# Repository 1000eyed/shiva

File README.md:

# SHIVA
A 12U 40% keyboard supporting multiple layouts, offset space bar row, and LEDs.

## About

This keyboard supports as many different layouts as possible. Currently supported are: ortho, alpha stagger, uniform 0.25U stagger, normal stagger, plus multiple space row configurations. After all, you got 5 PCBs.
- designed around Gateron KS27/KS33 low profile switches.
- rotary encoder support.
- bluetooth connection only. USB connection possible with an appropriate case.
- leds to display connection/battery status.
- nice!nano MCU.
- ZMK keyboard firmware support.
- open source.

## KLE

See possible configurations below:

## How to build one

I provide all the production files you will need in order to assemble the keyboard. In [prod](prod/) folder you will find the PCB gerbers and STLs for case (only one configuration is supported now). I intended the case to be CNC'd from PC, however it is not tested yet and only 3D printed it so far. There are no build instructions, as everything should be self-explanatory.

### Part list
| #     | name                 | comments                                  |
|-------|----------------------|-------------------------------------------|
| 1     | main PCB             | Order at fabricator of your choice        |
| 1     | Nice!nano v2         | Controller board. Make sure you have enough sockets for all pins. |
| 1     | EC11                 | Rotary Encoder through hole style (optional)         |
| ~45   | 1N4148 - SOD-123     | Diodes                                    |
| 3     | LED 3mm              | Choose red, yellow (orange), and green        |
| 1     | MSK-12C02            | Power switch                              | 
| 1     | JST 1.25mm pitch     | Battery connector, 2pin. I used S2B-PH-K-S(LF)(SN)        |
| 1     | 3.7V LiPo            | Battery                     |
| ~45   | KS33 or KS27         | Gateron Low Profile switches              |
| ~45   | Keycaps              | MX-compatible keycaps of your choice      |

My personal ZMK config: https://github.com/1000eyed/zmk-config-shiva

## Open source

In [source](source/) directory you will find the source files for the PCB and the case. You may use them however you like, I kindly ask you though to link back to my project, should you build it or update something.

## Gallery

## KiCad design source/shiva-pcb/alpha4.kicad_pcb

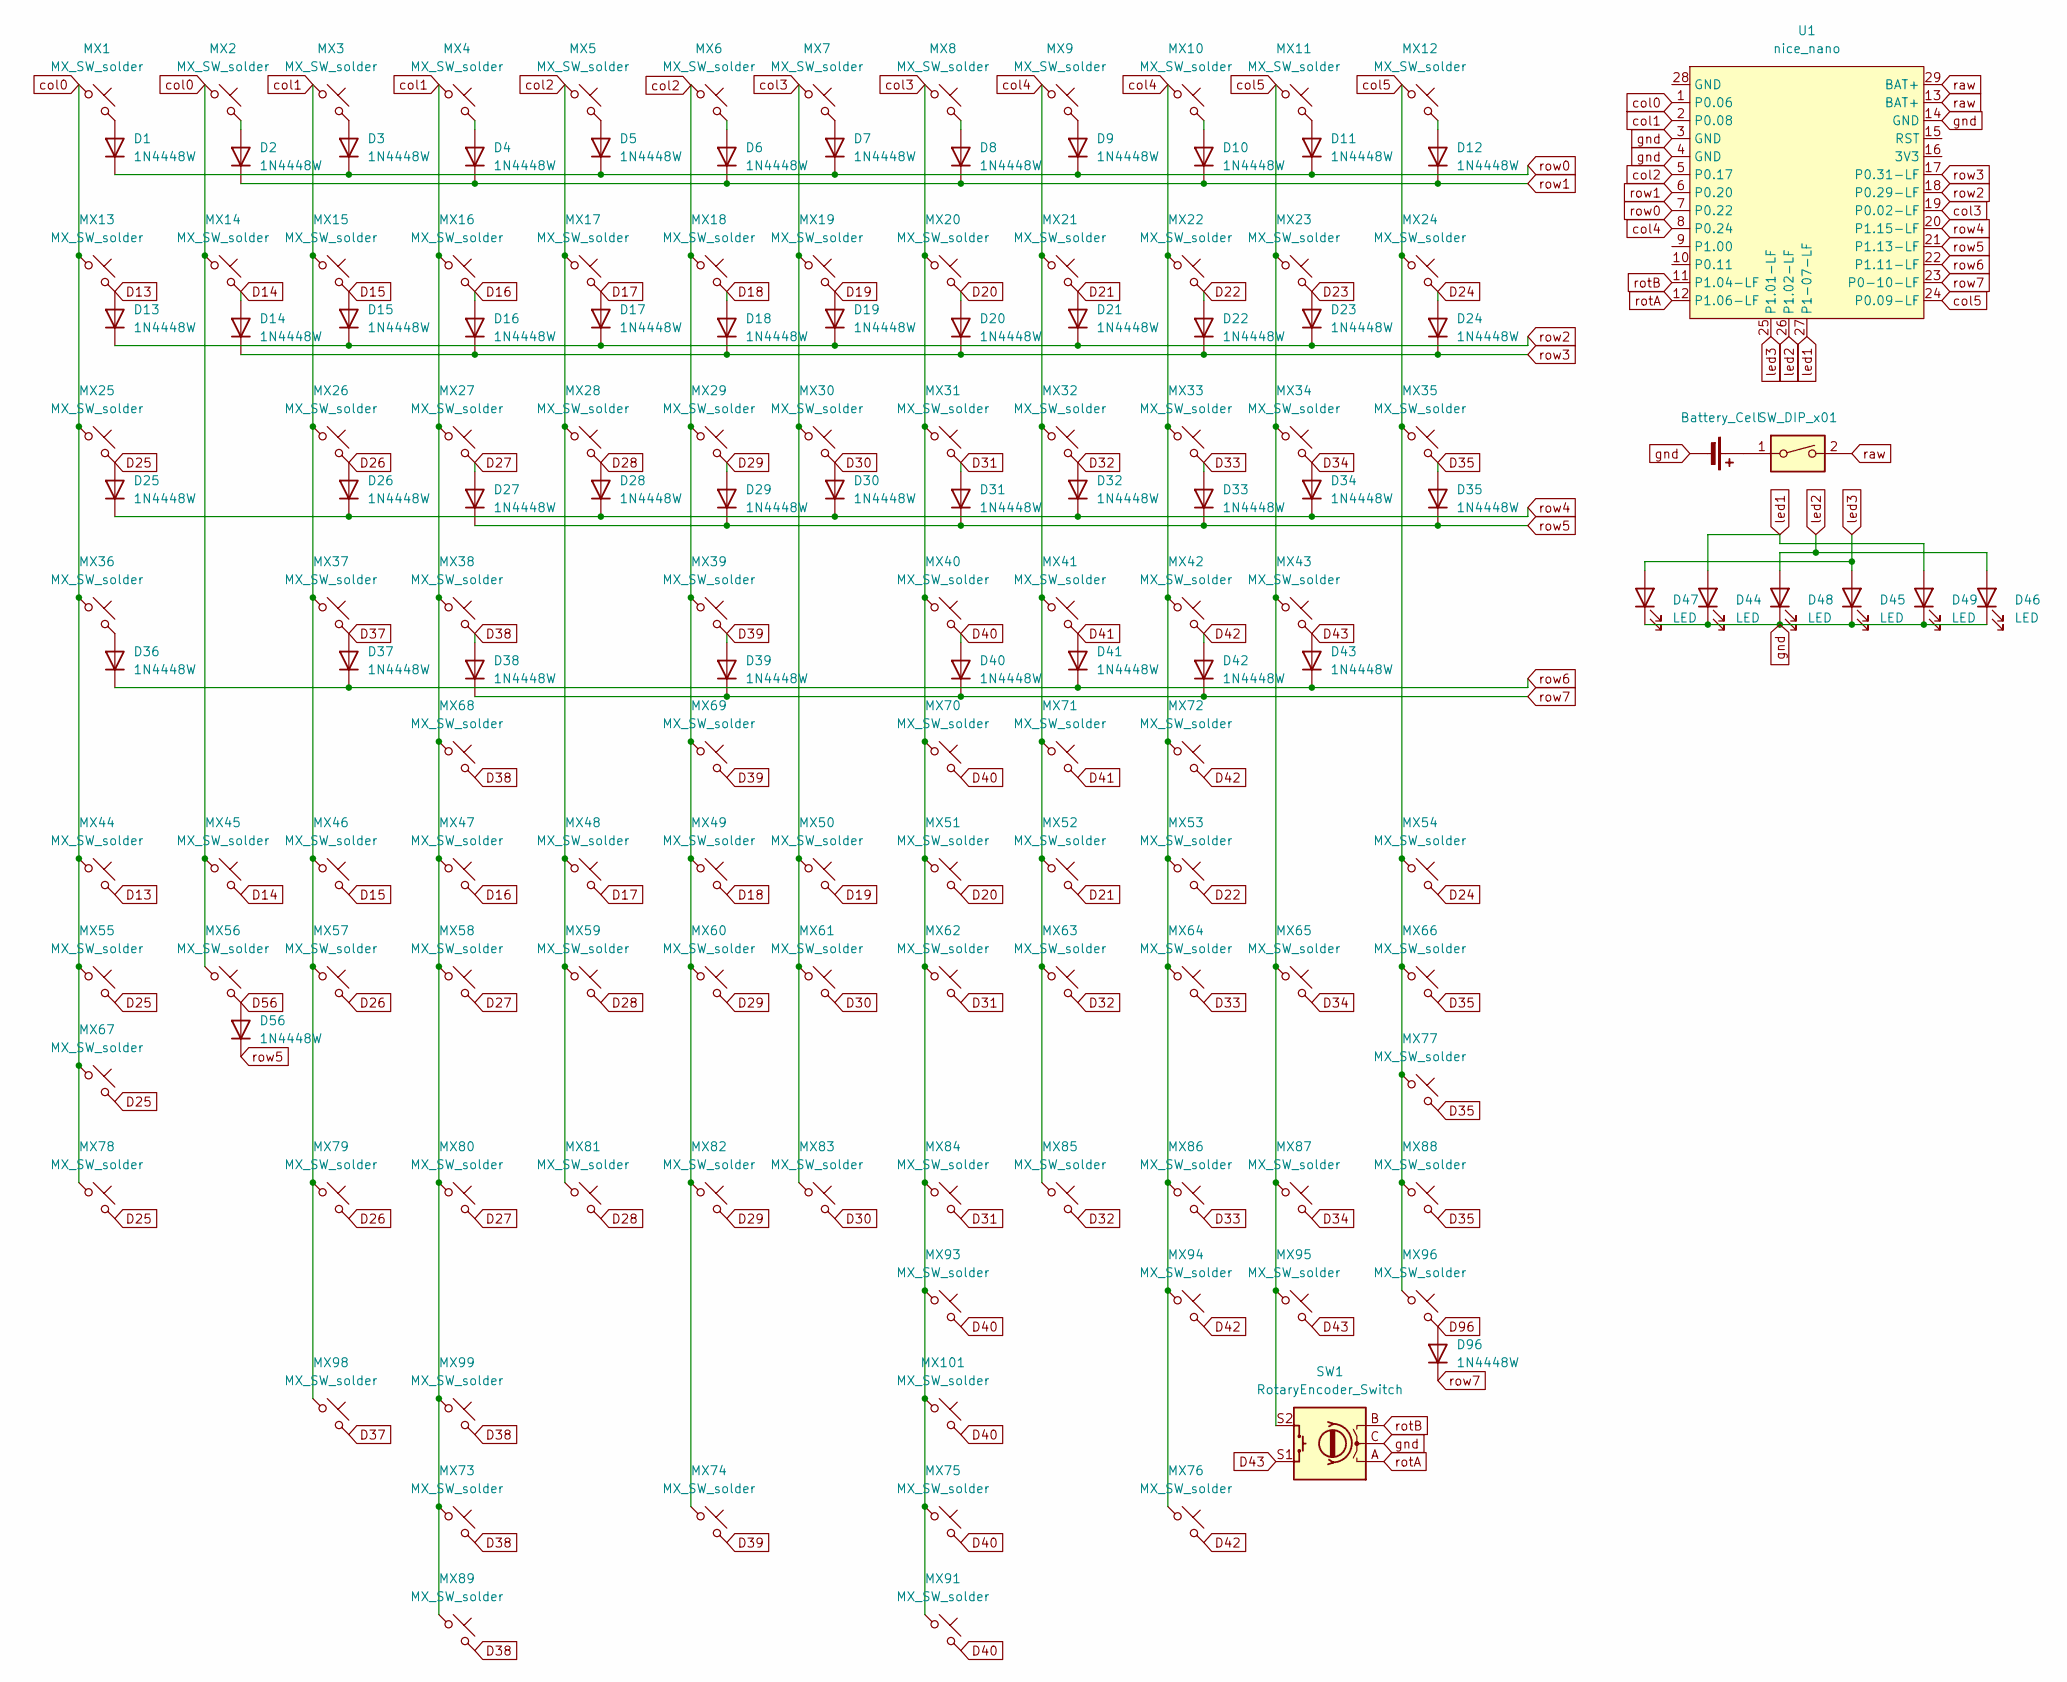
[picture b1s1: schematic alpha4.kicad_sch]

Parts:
BT1: Battery_Cell; JST_PH_S2B-PH-K_1x02_P2.00mm_Horizontal
D1, D2, D3, D4, D5, D6, D7, D8, D9, D10, D11, D12, D13, D14, D15, D16, D17, D18, D19, D20, D21, D22, D23, D24, D25, D26, D27, D28, D29, D30, D31, D32, D33, D34, D35, D36, D37, D38, D39, D40, D41, D42, D43, D56, D96: 1N4448W; D_SOD-123 invisible designator
D44, D45, D46, D47, D48, D49: LED; LED_D3.0mm
MX1, MX2, MX3, MX4, MX5, MX6, MX7, MX8, MX9, MX10, MX11, MX12, MX13, MX14, MX15, MX16, MX17, MX18, MX19, MX20, MX21, MX22, MX23, MX24, MX25, MX26, MX27, MX28, MX29, MX30, MX31, MX32, MX33, MX34, MX35, MX36, MX37, MX38, MX39, MX40, MX41, MX42, MX43, MX44, MX45, MX46, MX47, MX48, MX49, MX50, MX51, MX52, MX53, MX54, MX55, MX56, MX57, MX58, MX59, MX60, MX61, MX62, MX63, MX64, MX65, MX66, MX67, MX68, MX69, MX70, MX71, MX72, MX73, MX74, MX75, MX76, MX77, MX78, MX79, MX80, MX81, MX82, MX83, MX84, MX85, MX86, MX87, MX88, MX89, MX91, MX93, MX94, MX95, MX96, MX98, MX99, MX101: MX_SW_solder; gateron-ks27
SW1: RotaryEncoder_Switch; ROT_Alps_EC11E-Switch
SW2: SW_DIP_x01; SW_MSK12C02-HB
U1: nice_nano; nice_nano_AH_USBup

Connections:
D13: D13.2 (A), MX13.2, MX44.2
D14: D14.2 (A), MX14.2, MX45.2
D15: D15.2 (A), MX15.2, MX46.2
D16: D16.2 (A), MX16.2, MX47.2
D17: D17.2 (A), MX17.2, MX48.2
D18: D18.2 (A), MX18.2, MX49.2
D19: D19.2 (A), MX19.2, MX50.2
D20: D20.2 (A), MX20.2, MX51.2
D21: D21.2 (A), MX21.2, MX52.2
D22: D22.2 (A), MX22.2, MX53.2
D23: D23.2 (A), MX23.2
D24: D24.2 (A), MX24.2, MX54.2
D25: D25.2 (A), MX25.2, MX55.2, MX67.2, MX78.2
D26: D26.2 (A), MX26.2, MX57.2, MX79.2
D27: D27.2 (A), MX27.2, MX58.2, MX80.2
D28: D28.2 (A), MX28.2, MX59.2, MX81.2
D29: D29.2 (A), MX29.2, MX60.2, MX82.2
D30: D30.2 (A), MX30.2, MX61.2, MX83.2
D31: D31.2 (A), MX31.2, MX62.2, MX84.2
D32: D32.2 (A), MX32.2, MX63.2, MX85.2
D33: D33.2 (A), MX33.2, MX64.2, MX86.2
D34: D34.2 (A), MX34.2, MX65.2, MX87.2
D35: D35.2 (A), MX35.2, MX66.2, MX77.2, MX88.2
D37: D37.2 (A), MX37.2, MX98.2
D38: D38.2 (A), MX38.2, MX68.2, MX73.2, MX89.2, MX99.2
D39: D39.2 (A), MX39.2, MX69.2, MX74.2
D40: D40.2 (A), MX40.2, MX70.2, MX75.2, MX91.2, MX93.2, MX101.2
D41: D41.2 (A), MX41.2, MX71.2
D42: D42.2 (A), MX42.2, MX72.2, MX76.2, MX94.2
D43: D43.2 (A), MX43.2, MX95.2, SW1.S1
D56: D56.2 (A), MX56.2
D96: D96.2 (A), MX96.2
unnamed: BT1.1 (+), SW2.1
unnamed: D1.2 (A), MX1.2
unnamed: D2.2 (A), MX2.2
unnamed: D3.2 (A), MX3.2
unnamed: D4.2 (A), MX4.2
unnamed: D5.2 (A), MX5.2
unnamed: D6.2 (A), MX6.2
unnamed: D7.2 (A), MX7.2
unnamed: D8.2 (A), MX8.2
unnamed: D9.2 (A), MX9.2
unnamed: D10.2 (A), MX10.2
unnamed: D11.2 (A), MX11.2
unnamed: D12.2 (A), MX12.2
unnamed: D36.2 (A), MX36.2
col0: MX1.1, MX2.1, MX13.1, MX14.1, MX25.1, MX36.1, MX44.1, MX45.1, MX55.1, MX56.1, MX67.1, MX78.1, U1.1 (P0.06)
col1: MX3.1, MX4.1, MX15.1, MX16.1, MX26.1, MX27.1, MX37.1, MX38.1, MX46.1, MX47.1, MX57.1, MX58.1, MX68.1, MX73.1, MX79.1, MX80.1, MX89.1, MX98.1, MX99.1, U1.2 (P0.08)
col2: MX5.1, MX6.1, MX17.1, MX18.1, MX28.1, MX29.1, MX39.1, MX48.1, MX49.1, MX59.1, MX60.1, MX69.1, MX74.1, MX81.1, MX82.1, U1.5 (P0.17)
col3: MX7.1, MX8.1, MX19.1, MX20.1, MX30.1, MX31.1, MX40.1, MX50.1, MX51.1, MX61.1, MX62.1, MX70.1, MX75.1, MX83.1, MX84.1, MX91.1, MX93.1, MX101.1, U1.19 (P0.02-LF)
col4: MX9.1, MX10.1, MX21.1, MX22.1, MX32.1, MX33.1, MX41.1, MX42.1, MX52.1, MX53.1, MX63.1, MX64.1, MX71.1, MX72.1, MX76.1, MX85.1, MX86.1, MX94.1, U1.8 (P0.24)
col5: MX11.1, MX12.1, MX23.1, MX24.1, MX34.1, MX35.1, MX43.1, MX54.1, MX65.1, MX66.1, MX77.1, MX87.1, MX88.1, MX95.1, MX96.1, SW1.S2, U1.24 (P0.09-LF)
gnd: BT1.2 (-), D44.1 (K), D45.1 (K), D46.1 (K), D47.1 (K), D48.1 (K), D49.1 (K), SW1.C, U1.3 (GND), U1.4 (GND), U1.14 (GND)
led1: D44.2 (A), D49.2 (A), U1.27 (P1-07-LF)
led2: D46.2 (A), D48.2 (A), U1.26 (P1.02-LF)
led3: D45.2 (A), D47.2 (A), U1.25 (P1.01-LF)
raw: SW2.2, U1.13 (BAT+), U1.29 (BAT+)
rotA: SW1.A, U1.12 (P1.06-LF)
rotB: SW1.B, U1.11 (P1.04-LF)
row0: D1.1 (K), D3.1 (K), D5.1 (K), D7.1 (K), D9.1 (K), D11.1 (K), U1.7 (P0.22)
row1: D2.1 (K), D4.1 (K), D6.1 (K), D8.1 (K), D10.1 (K), D12.1 (K), U1.6 (P0.20)
row2: D13.1 (K), D15.1 (K), D17.1 (K), D19.1 (K), D21.1 (K), D23.1 (K), U1.18 (P0.29-LF)
row3: D14.1 (K), D16.1 (K), D18.1 (K), D20.1 (K), D22.1 (K), D24.1 (K), U1.17 (P0.31-LF)
row4: D25.1 (K), D26.1 (K), D28.1 (K), D30.1 (K), D32.1 (K), D34.1 (K), U1.20 (P1.15-LF)
row5: D27.1 (K), D29.1 (K), D31.1 (K), D33.1 (K), D35.1 (K), D56.1 (K), U1.21 (P1.13-LF)
row6: D36.1 (K), D37.1 (K), D41.1 (K), D43.1 (K), U1.22 (P1.11-LF)
row7: D38.1 (K), D39.1 (K), D40.1 (K), D42.1 (K), D96.1 (K), U1.23 (P0-10-LF)

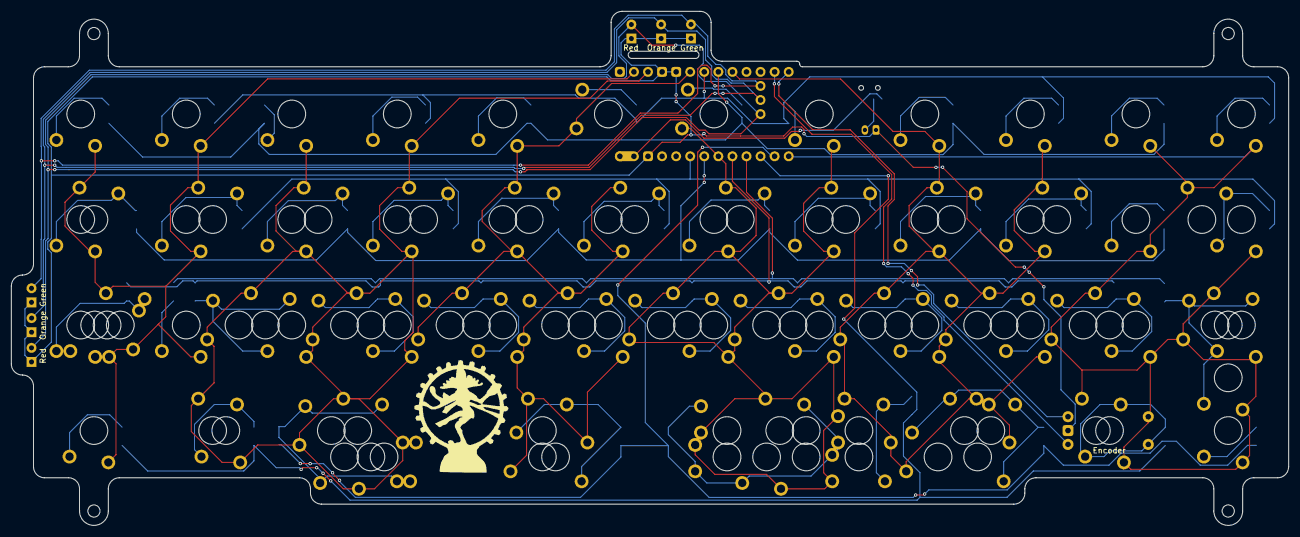
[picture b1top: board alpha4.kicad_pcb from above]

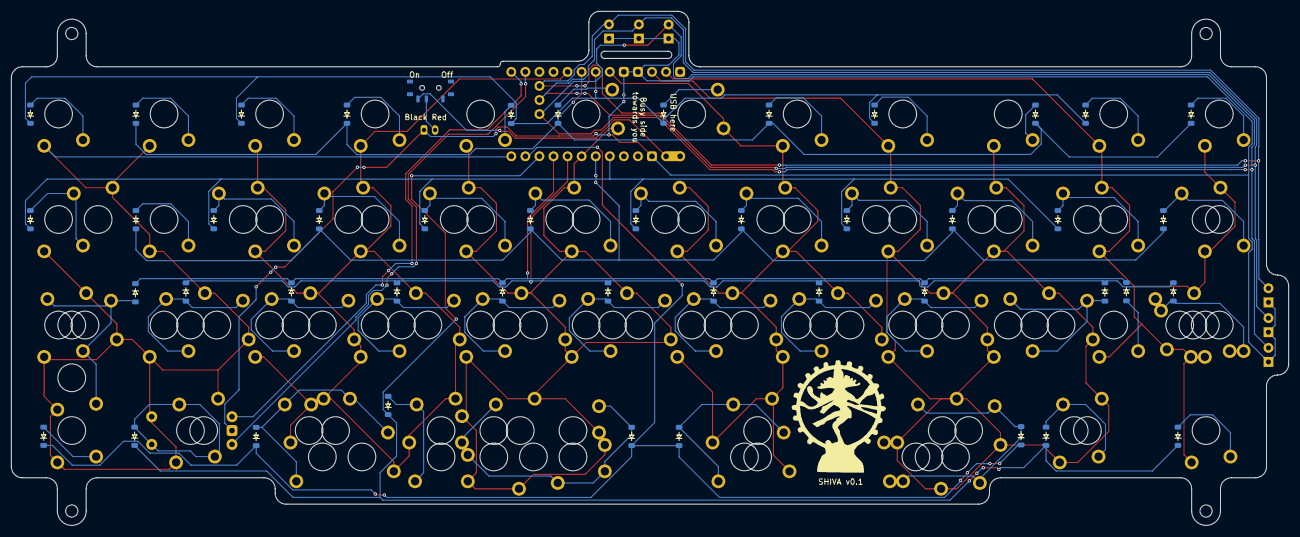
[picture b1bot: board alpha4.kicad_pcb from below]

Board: 2 copper layers, 230.6 x 92.8 mm, 152 parts (48 on the bottom side), 67 nets.

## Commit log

2024-06-22 Initial commit.
2024-06-22 add kle pic
2024-07-07 Create shiva-case
2024-07-07 Create mock
2024-11-22 Rename shiva assort.jpg to shiva_assort.jpg
